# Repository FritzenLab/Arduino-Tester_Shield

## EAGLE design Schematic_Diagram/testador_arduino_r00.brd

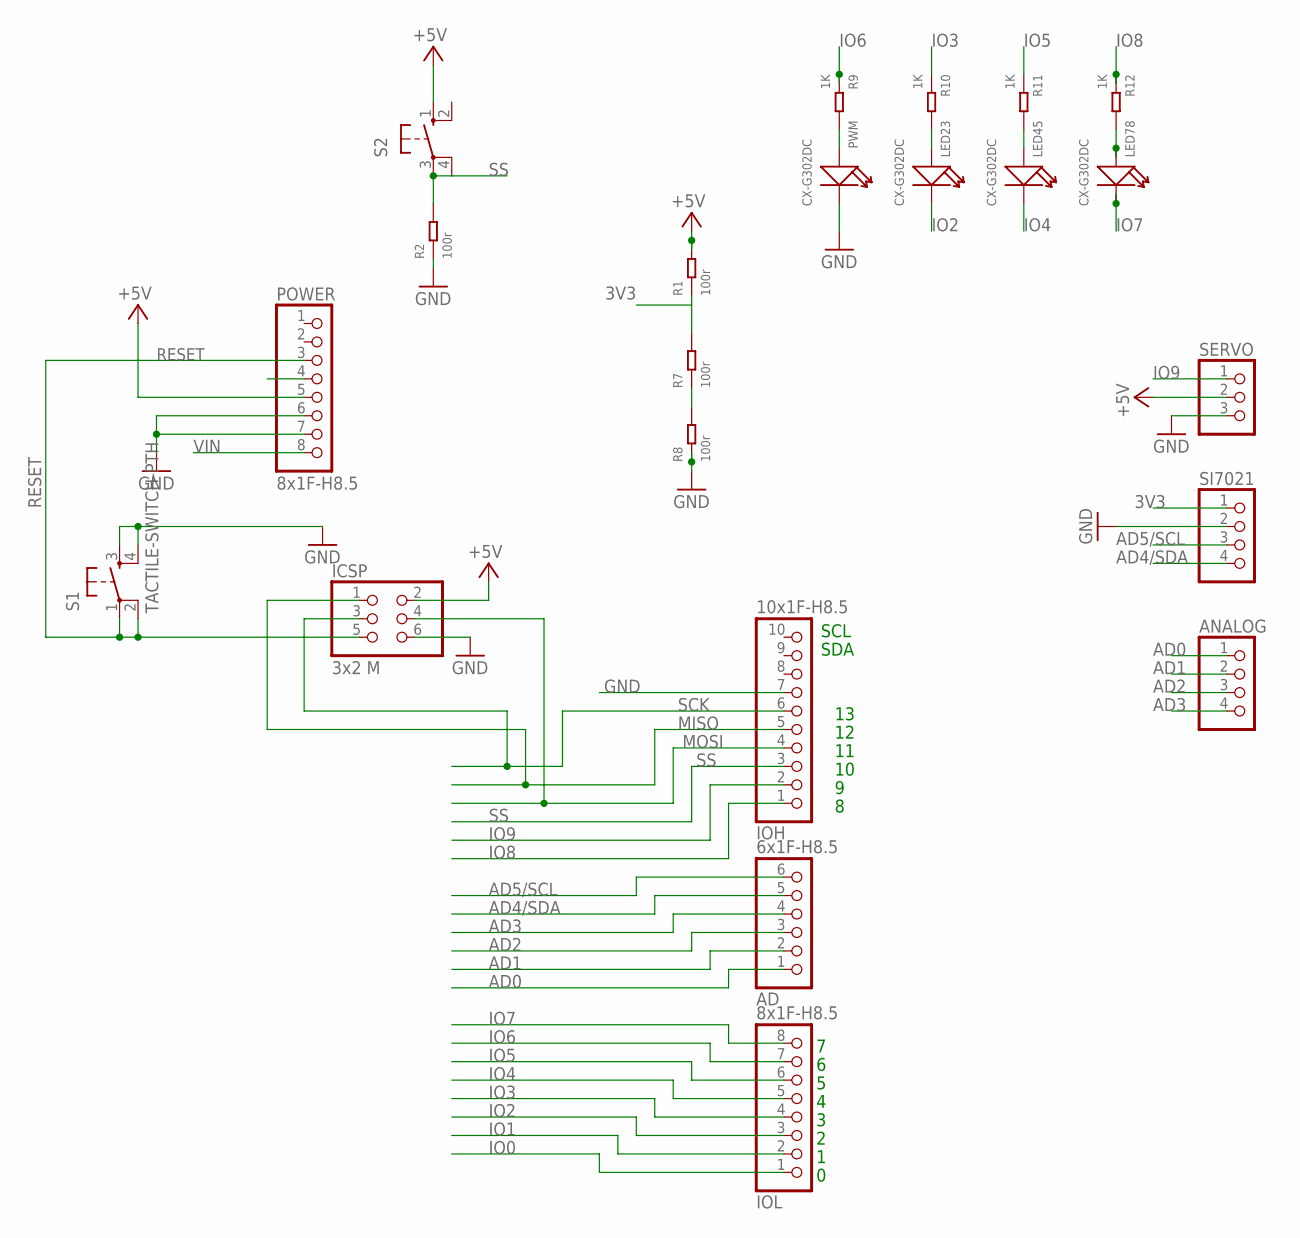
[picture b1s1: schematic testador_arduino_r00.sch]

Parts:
AD: 6x1F-H8.5; 1X06
ANALOG: PINHD-1X4; 1X04
ICSP: 3x2 M; 2X03
IOH: 10x1F-H8.5; 1X10
IOL: 8x1F-H8.5; 1X08
LED23, LED45, LED78: CX-G302DC; LED2-2.54-D3.0MM
POWER: 8x1F-H8.5; 1X08
PWM: CX-G302DC; LED2-2.54-D3.0MM
R1, R2, R7, R8: 100r; PR-D2.3XL6.5MM
R9, R10, R11, R12: 1K; PR-D2.3XL6.5MM
S1: TACTILE-SWITCH-PTH; TAC-SWITCH-PTH
S2: 40-XX; B3F-40XX
SERVO: PINHD-1X3; 1X03
SI7021: PINHD-1X4; 1X04

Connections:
3V3: R1.1, R7.2, SI7021.1
+5V: ICSP.2, POWER.5, R1.2, S2.1 (S), SERVO.2
AD0: AD.1, ANALOG.1
AD1: AD.2, ANALOG.2
AD2: AD.3, ANALOG.3
AD3: AD.4, ANALOG.4
AD4/SDA: AD.5, SI7021.4
AD5/SCL: AD.6, SI7021.3
GND: ICSP.6, IOH.7, POWER.6, POWER.7, PWM.K (-), R2.1, R8.1, S1.3, S1.4, SERVO.3, SI7021.2
IO0: IOL.1
IO1: IOL.2
IO2: IOL.3, LED23.K (-)
IO3: IOL.4, R10.1
IO4: IOL.5, LED45.K (-)
IO5: IOL.6, R11.1
IO6: IOL.7, R9.1
IO7: IOL.8, LED78.K (-)
IO8: IOH.1, R12.1
IO9: IOH.2, SERVO.1
MISO: ICSP.1, IOH.5
MOSI: ICSP.4, IOH.4
unnamed: R7.1, R8.2
unnamed: PWM.A (+), R9.2
unnamed: LED23.A (+), R10.2
unnamed: LED45.A (+), R11.2
unnamed: LED78.A (+), R12.2
RESET: ICSP.5, POWER.3, S1.1, S1.2
SCK: ICSP.3, IOH.6
SS: IOH.3, R2.2, S2.3, S2.4 (P1)
VIN: POWER.8

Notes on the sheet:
SDA
SCL

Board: 2 copper layers, 22 parts (0 on the bottom side), 27 nets, no tracks yet.

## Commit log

2016-03-25 initial release of the Arduino-tester Shield
    initial release of the Arduino-tester Shield, containing shield
    schematics and code for analog inputs, digital inputs, digital outputs,
    PWM and servo

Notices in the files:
parts and their libraries:
GeekAmmo: Licensing:Creative Commons ShareAlike 4.0 International - https://creativecommons.org/licenses/by-sa/4.0
